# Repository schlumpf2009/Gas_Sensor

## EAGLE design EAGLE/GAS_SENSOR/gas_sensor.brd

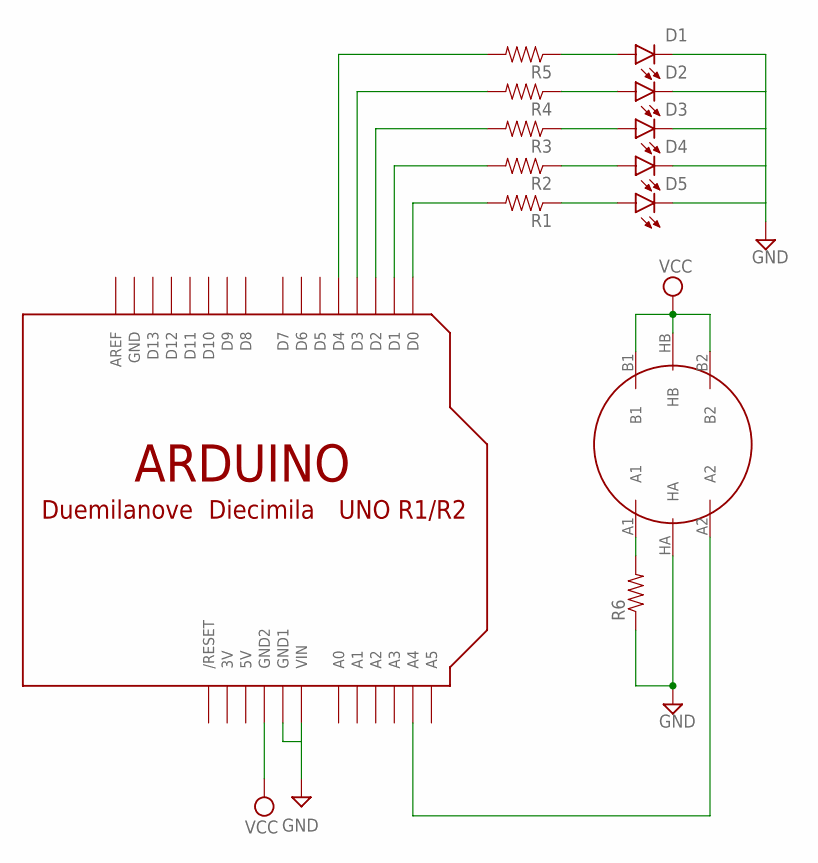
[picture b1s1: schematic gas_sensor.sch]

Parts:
D1, D2, D3, D4, D5: LED3MM
R1, R2, R3, R4, R5, R6: RESISTORAXIAL-0.3; AXIAL-0.3
U$1: METHANE_SENSOR; MQ-3
U$2: ARDUINOUNO; ARDUINO

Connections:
3V: U$2.3V
5V: U$2.5V
GND: D1.K (C), D2.K (C), D3.K (C), D4.K (C), D5.K (C), R6.P$1 (1), U$1.HA, U$2.GND
GND1: U$2.GND1
GND2: U$2.GND2
unnamed: R5.P$2 (2), U$2.D4
unnamed: R4.P$2 (2), U$2.D3
unnamed: R3.P$2 (2), U$2.D2
unnamed: R2.P$2 (2), U$2.D1
unnamed: R1.P$2 (2), U$2.D0
unnamed: D1.A, R5.P$1 (1)
unnamed: D2.A, R4.P$1 (1)
unnamed: D3.A, R3.P$1 (1)
unnamed: D4.A, R2.P$1 (1)
unnamed: D5.A, R1.P$1 (1)
unnamed: R6.P$2 (2), U$1.A1
VCC: U$1.B1, U$1.B2, U$1.HB
VIN: U$2.VIN

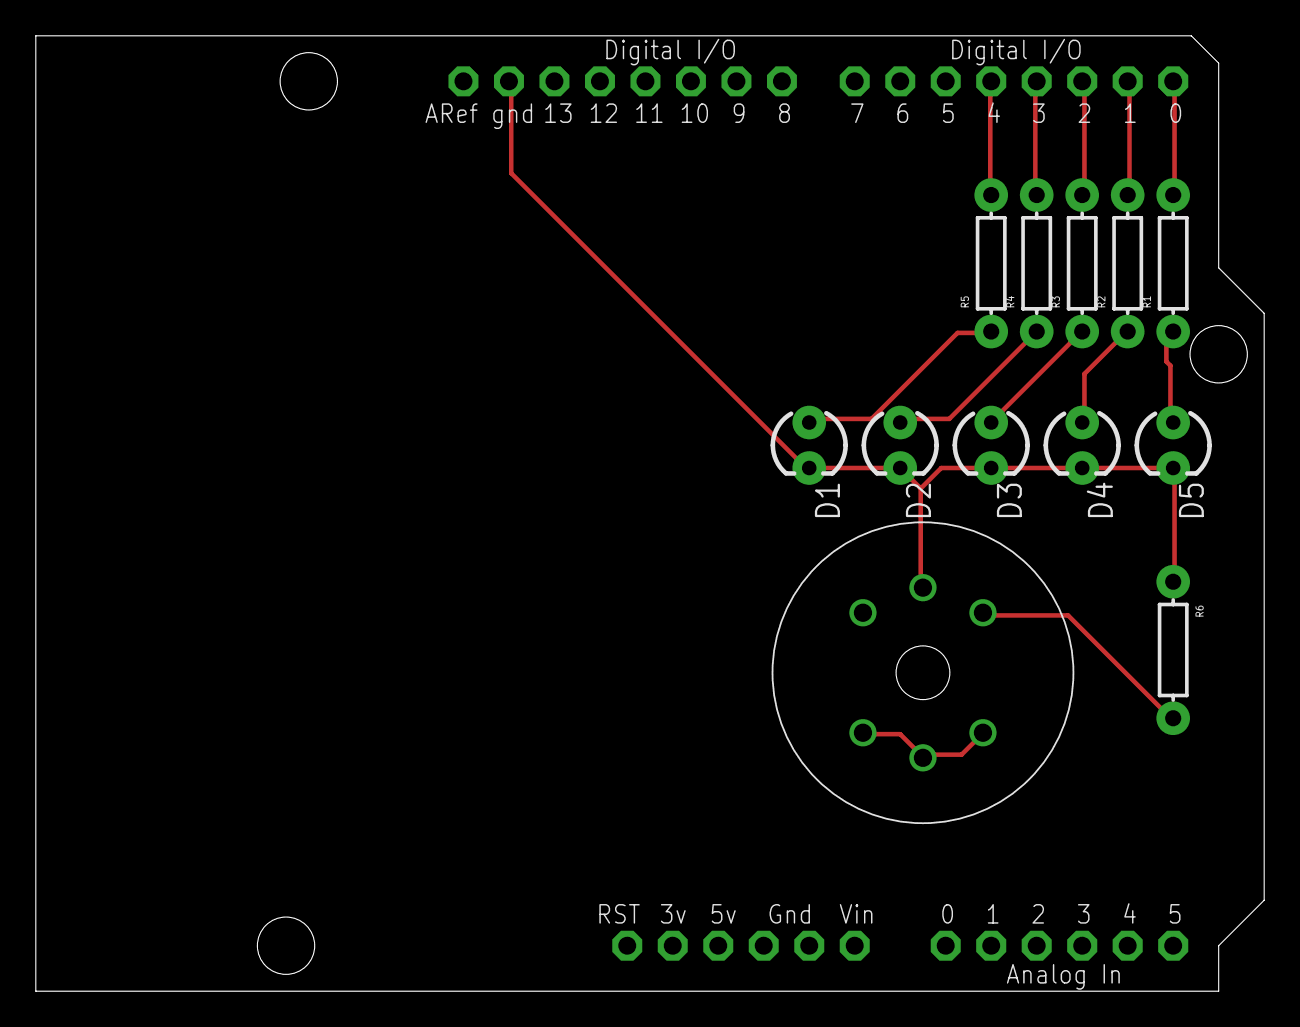
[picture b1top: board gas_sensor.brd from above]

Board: 2 copper layers, 68.6 x 53.3 mm, 13 parts (0 on the bottom side), 13 nets.

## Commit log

2016-11-16 commit source .cpp file
2016-11-16 Uploading EAGLE Files

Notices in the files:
parts and their libraries:
SparkFun-LED: Licensing: Creative Commons ShareAlike 4.0 International - https://creativecommons.org/licenses/by-sa/4.0
